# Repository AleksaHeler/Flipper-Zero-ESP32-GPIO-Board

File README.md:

# Flipper-Zero-ESP32-GPIO-Board
 A custom ESP32 board for Flipper Zero GPIO connector

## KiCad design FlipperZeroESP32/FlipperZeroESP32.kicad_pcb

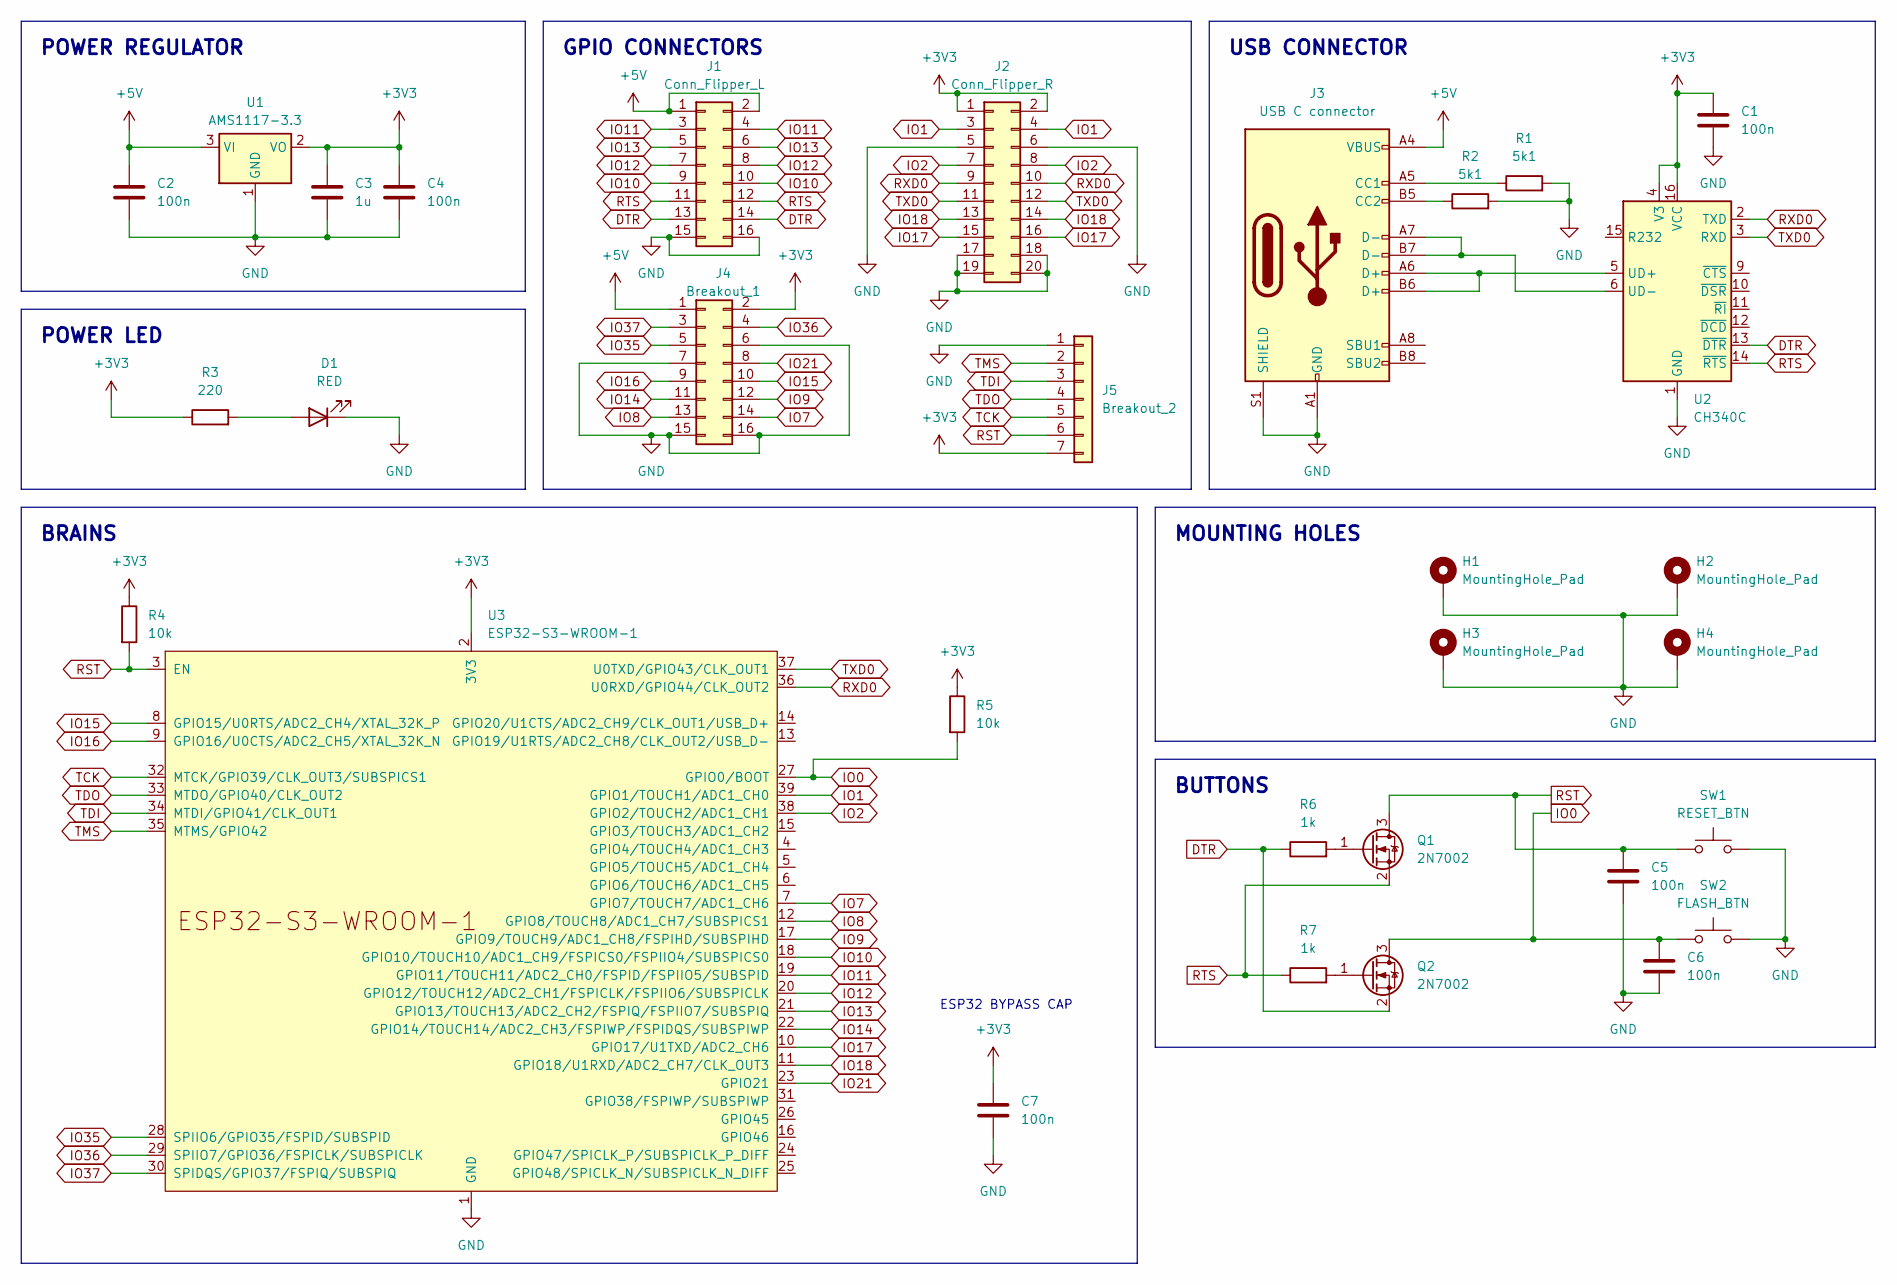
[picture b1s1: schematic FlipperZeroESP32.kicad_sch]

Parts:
C1, C2, C4, C5, C6, C7: 100n; C_1206_3216Metric
C3: 1u; C_1206_3216Metric
D1: RED; LED_D5.0mm
H1, H2, H3, H4: MountingHole_Pad; MountingHole_3.2mm_M3_Pad_Via
J1: Conn_Flipper_L; PinHeader_2x08_P2.54mm_Vertical
J2: Conn_Flipper_R; PinHeader_2x10_P2.54mm_Vertical
J3: USB C connector; USB_C_Receptacle_G-Switch_GT-USB-7010ASV
J4: Breakout_1; PinHeader_2x08_P2.54mm_Vertical
J5: Breakout_2; PinHeader_1x07_P2.54mm_Vertical
Q1, Q2: 2N7002; SOT-23
R1, R2: 5k1; R_1206_3216Metric
R3: 220; R_1206_3216Metric
R4, R5: 10k; R_1206_3216Metric
R6, R7: 1k; R_1206_3216Metric
SW1: RESET_BTN; SW_PUSH_6mm
SW2: FLASH_BTN; SW_PUSH_6mm
U1: AMS1117-3.3; SOT-223-3_TabPin2
U2: CH340C; SOIC-16_3.9x9.9mm_P1.27mm
U3: ESP32-S3-WROOM-1

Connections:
+3V3: C1.1, C3.1, C4.1, C7.1, J2.1, J2.2, J4.2, J5.7, R3.1, R4.1, R5.1, U1.2 (VO), U2.4 (V3), U2.16 (VCC), U3.2 (3V3)
+5V: C2.1, J1.1, J1.2, J3.A4 (VBUS), J3.A9 (VBUS), J3.B4 (VBUS), J3.B9 (VBUS), J4.1, U1.3 (VI)
DTR: J1.13, J1.14, Q2.2 (S), R6.1, U2.13 (~DTR)
GND: C1.2, C2.2, C3.2, C4.2, C5.2, C6.2, C7.2, D1.1 (K), H1.1, H2.1, H3.1, H4.1, J1.15, J1.16, J2.5, J2.6, J2.17, J2.18, J2.19, J2.20, J3.A1 (GND), J3.A12 (GND), J3.B1 (GND), J3.B12 (GND), J3.S1 (SHIELD), J4.6, J4.7, J4.15, J4.16, J5.1, R1.2, R2.2, SW1.2, SW2.2, U1.1 (GND), U2.1 (GND), U3.1 (GND), U3.40 (GND), U3.41 (GND)
IO0: C6.1, Q2.3 (D), R5.2, SW2.1, U3.27 (GPIO0/BOOT)
IO1: J2.3, J2.4, U3.39 (GPIO1/TOUCH1/ADC1_CH0)
IO2: J2.7, J2.8, U3.38 (GPIO2/TOUCH2/ADC1_CH1)
IO7: J4.14, U3.7 (GPIO7/TOUCH7/ADC1_CH6)
IO8: J4.13, U3.12 (GPIO8/TOUCH8/ADC1_CH7/SUBSPICS1)
IO9: J4.12, U3.17 (GPIO9/TOUCH9/ADC1_CH8/FSPIHD/SUBSPIHD)
IO10: J1.9, J1.10, U3.18 (GPIO10/TOUCH10/ADC1_CH9/FSPICS0/FSPIIO4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)
IO11: J1.3, J1.4, U3.19 (GPIO11/TOUCH11/ADC2_CH0/FSPID/FSPIIO5/S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)
IO12: J1.7, J1.8, U3.20 (GPIO12/TOUCH12/ADC2_CH1/FSPICLK/FSPIIO6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)
IO13: J1.5, J1.6, U3.21 (GPIO13/TOUCH13/ADC2_CH2/FSPIQ/FSPIIO7/S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)
IO14: J4.11, U3.22 (GPIO14/TOUCH14/ADC2_CH3/FSPIWP/FSPIDQS/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)
IO15: J4.10, U3.8 (GPIO15/U0RTS/ADC2_CH4/XTAL_32K_P)
IO16: J4.9, U3.9 (GPIO16/U0CTS/ADC2_CH5/XTAL_32K_N)
IO17: J2.15, J2.16, U3.10 (GPIO17/U1TXD/ADC2_CH6)
IO18: J2.13, J2.14, U3.11 (GPIO18/U1RXD/ADC2_CH7/CLK_OUT3)
IO21: J4.8, U3.23 (GPIO21)
IO35: J4.5, U3.28 (SPIIO6/GPIO35/FSPID/SUBSPID)
IO36: J4.4, U3.29 (SPIIO7/GPIO36/FSPICLK/SUBSPICLK)
IO37: J4.3, U3.30 (SPIDQS/GPIO37/FSPIQ/SUBSPIQ)
unnamed: D1.2 (A), R3.2
unnamed: J3.A5 (CC1), R1.1
unnamed: J3.B5 (CC2), R2.1
unnamed: Q1.1 (G), R6.2
unnamed: Q2.1 (G), R7.2
unnamed: J3.A6 (D+), J3.B6 (D+), U2.5 (UD+)
unnamed: J3.A7 (D-), J3.B7 (D-), U2.6 (UD-)
RST: C5.1, J5.6, Q1.3 (D), R4.2, SW1.1, U3.3 (EN)
RTS: J1.11, J1.12, Q1.2 (S), R7.1, U2.14 (~RTS)
RXD0: J2.9, J2.10, U2.2 (TXD), U3.36 (U0RXD/GPIO44/CLK_OUT2)
TCK: J5.5, U3.32 (MTCK/GPIO39/CLK_OUT3/SUBSPICS1)
TDI: J5.3, U3.34 (MTDI/GPIO41/CLK_OUT1)
TDO: J5.4, U3.33 (MTDO/GPIO40/CLK_OUT2)
TMS: J5.2, U3.35 (MTMS/GPIO42)
TXD0: J2.11, J2.12, U2.3 (RXD), U3.37 (U0TXD/GPIO43/CLK_OUT1)

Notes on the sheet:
ESP32 BYPASS CAP
GPIO CONNECTORS
POWER REGULATOR
BRAINS
POWER LED
MOUNTING HOLES
USB CONNECTOR
BUTTONS

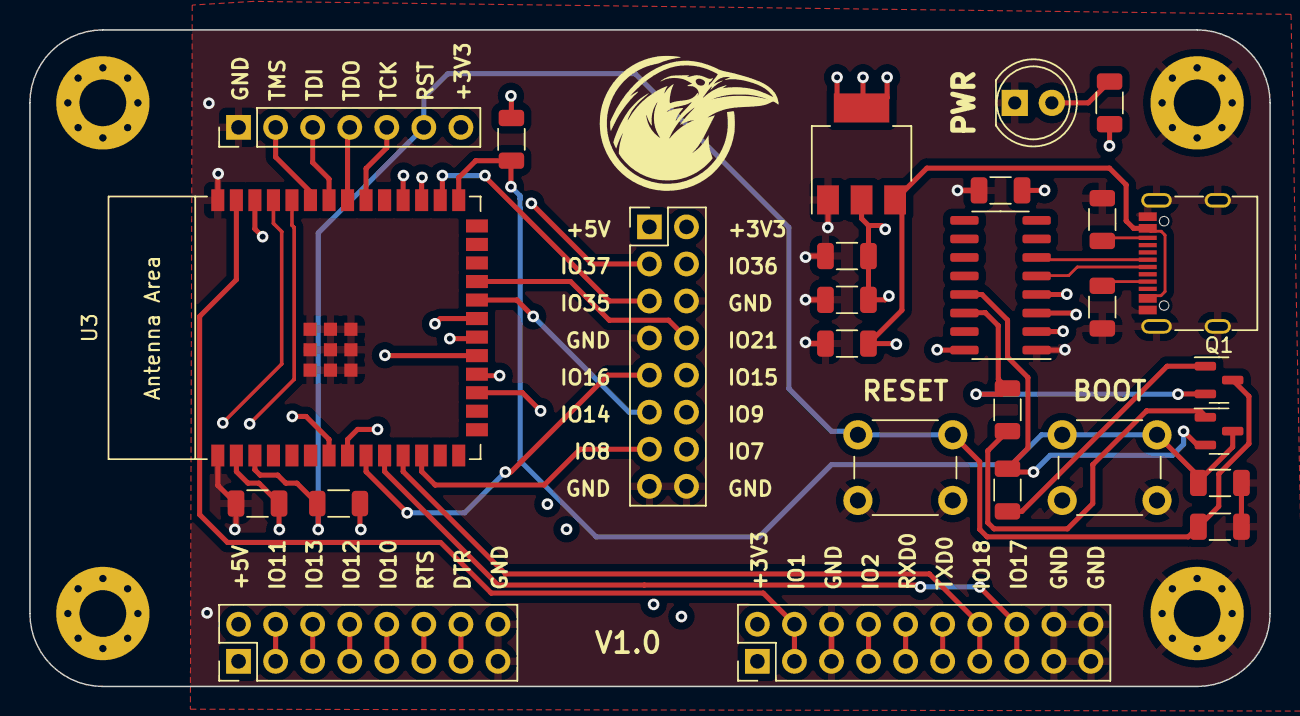
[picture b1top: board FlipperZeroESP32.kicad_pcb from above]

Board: 4 copper layers, 85.0 x 45.0 mm, 31 parts (0 on the bottom side), 38 nets.

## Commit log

2024-01-13 Add empty KiCAD project
2024-01-13 Finished sch, started PCB
2024-01-24 Start new hardware design
2024-01-27 Add marauder binary flasher
